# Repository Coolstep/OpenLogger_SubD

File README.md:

# OpenLogger_SubD
Based on OpenLog by SparkFun I created a SubD "Black Box" Dongle 

For more information see: http://fullstackengineer.tech/blog/2021/01/12/robust-black-box-for-mobile-applications/

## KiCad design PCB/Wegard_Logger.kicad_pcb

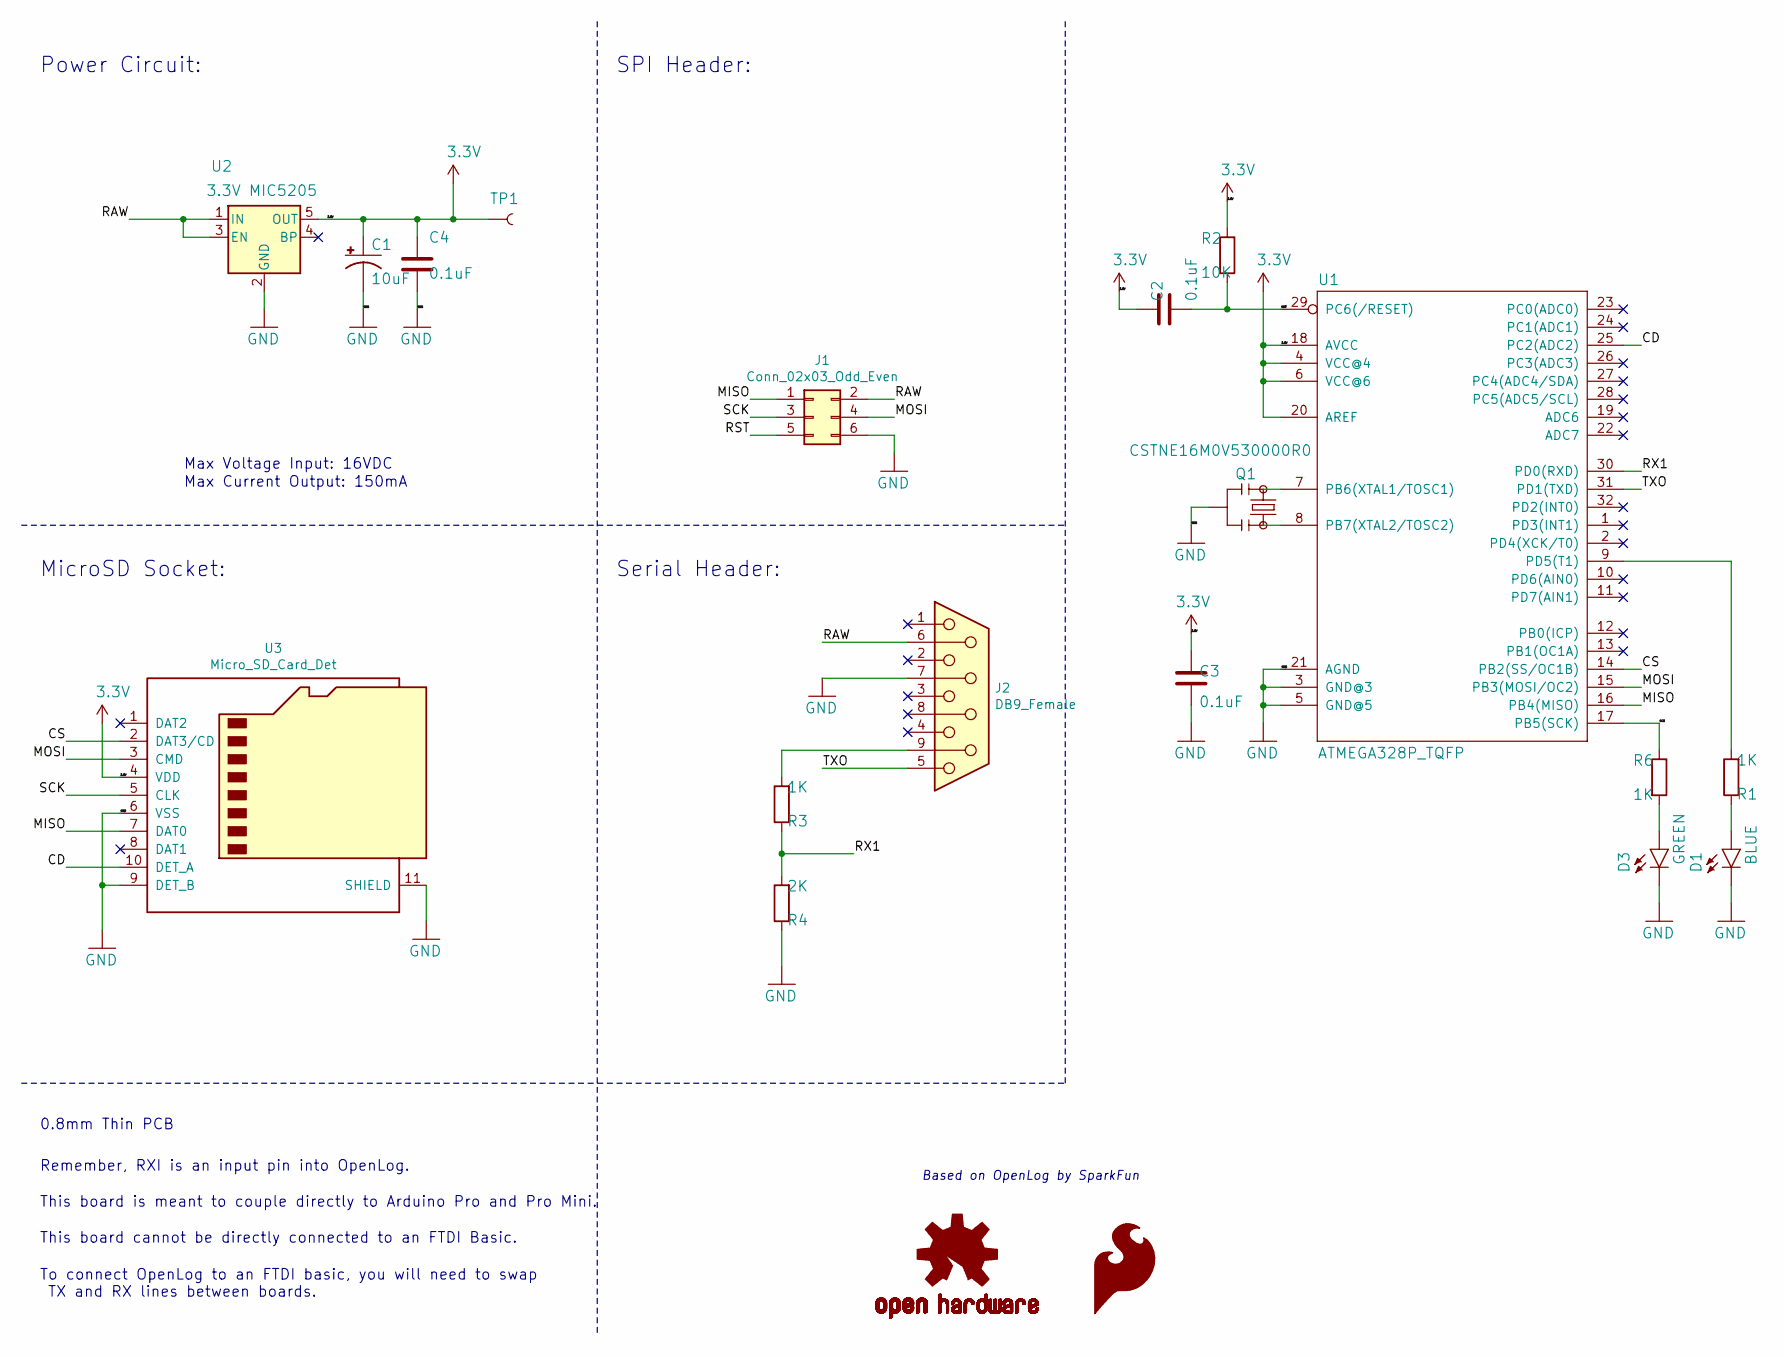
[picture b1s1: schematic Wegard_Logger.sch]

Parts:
C1: 10uF; 0603-POL
C2, C3, C4: 0.1uF; C_0603_1608Metric
D1: BLUE; LED-0603
D3: GREEN; LED-0603
J1: Conn_02x03_Odd_Even; Tag-Connect_TC2030-IDC-NL_2x03_P1.27mm_Vertical
J2: DB9_Female; DSUB-9_Female_EdgeMount_P2.77mm
Q1: CSTNE16M0V530000R0; Resonator_SMD_muRata_CSTxExxV-3Pin_3.0x1.1mm
R1, R3, R6: 1K; R_0603_1608Metric
R2: 10K; R_0603_1608Metric
R4: 2K; R_0603_1608Metric
TP1: TEST-POINT3; PAD.03X.03
U1: ATMEGA328P_TQFP; TQFP32-08
U2: 3.3V MIC5205; SOT-23-5
U3: Micro_SD_Card_Det; microSD_HC_Molex_104031-0811

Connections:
3.3V: C1.A (+), C2.2, C3.2, C4.1, R2.1, TP1.P$1, U1.4 (VCC@4), U1.6 (VCC@6), U1.18 (AVCC), U1.20 (AREF), U2.5 (OUT), U3.4 (VDD)
/CD: U1.25 (PC2(ADC2)), U3.10 (DET_A)
/CS: U1.14 (PB2(SS/OC1B)), U3.2 (DAT3/CD)
/MISO: J1.1, U1.16 (PB4(MISO)), U3.7 (DAT0)
/MOSI: J1.4, U1.15 (PB3(MOSI/OC2)), U3.3 (CMD)
/RAW: J1.2, J2.6, U2.1 (IN), U2.3 (EN)
/RST: C2.1, J1.5, R2.2, U1.29 (PC6(/RESET))
/RX1: R3.1, R4.2, U1.30 (PD0(RXD))
/SCK: J1.3, R6.1, U1.17 (PB5(SCK)), U3.5 (CLK)
/TXO: J2.5, U1.31 (PD1(TXD))
GND: C1.K (-), C3.1, C4.2, D1.C, D3.C, J1.6, J2.7, Q1.2, R4.1, U1.3 (GND@3), U1.5 (GND@5), U1.21 (AGND), U2.2 (GND), U3.6 (VSS), U3.9 (DET_B), U3.11 (SHIELD)
unnamed: D1.A, R1.1
unnamed: D3.A, R6.2
unnamed: J2.9, R3.2
unnamed: Q1.1, U1.8 (PB7(XTAL2/TOSC2))
unnamed: Q1.3, U1.7 (PB6(XTAL1/TOSC1))
unnamed: R1.2, U1.9 (PD5(T1))

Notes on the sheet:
Max Voltage Input: 16VDC
Max Current Output: 150mA
Remember, RXI is an input pin into OpenLog.
This board is meant to couple directly to Arduino Pro and Pro Mini.
This board cannot be directly connected to an FTDI Basic.
To connect OpenLog to an FTDI basic, you will need to swap TX and RX lines between boards.
0.8mm Thin PCB
Power Circuit:
Serial Header:
MicroSD Socket:
SPI Header:
Based on OpenLog by SparkFun

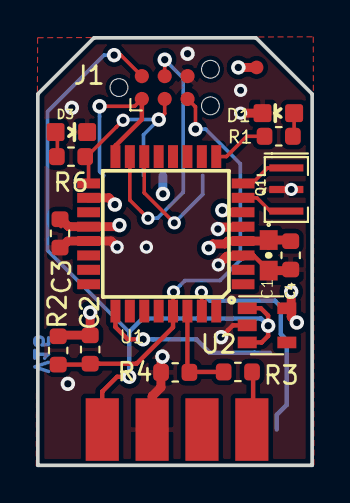
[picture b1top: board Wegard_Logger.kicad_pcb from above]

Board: 4 copper layers, 15.2 x 23.8 mm, 18 parts (0 on the bottom side), 17 nets.
